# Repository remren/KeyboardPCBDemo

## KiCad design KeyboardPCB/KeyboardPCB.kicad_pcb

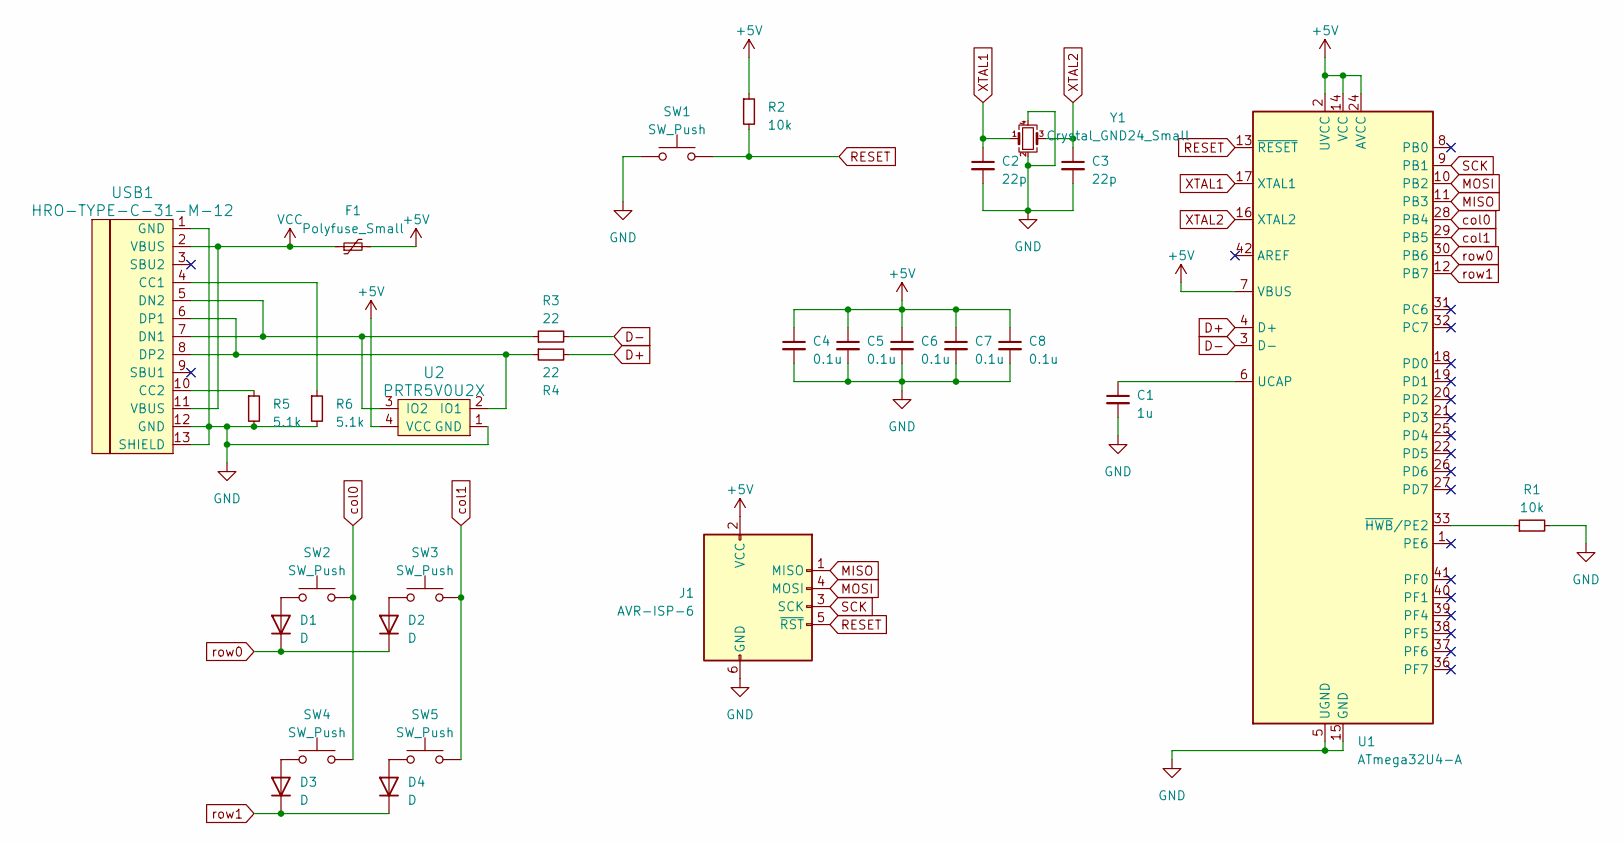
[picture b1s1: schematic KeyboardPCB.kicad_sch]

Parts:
C1: 1u; C_0805_2012Metric_Pad1.18x1.45mm_HandSolder
C2, C3: 22p; C_0805_2012Metric_Pad1.18x1.45mm_HandSolder
C4, C5, C6, C7, C8: 0.1u; C_0805_2012Metric_Pad1.18x1.45mm_HandSolder
D1, D2, D3, D4: D; D_SOD-123
F1: Polyfuse_Small; Fuse_1206_3216Metric_Pad1.42x1.75mm_HandSolder
J1: AVR-ISP-6; Reset_Pretty-Mask
R1, R2: 10k; R_0805_2012Metric_Pad1.20x1.40mm_HandSolder
R3, R4: 22; R_0805_2012Metric_Pad1.20x1.40mm_HandSolder
R5, R6: 5.1k; R_0805_2012Metric_Pad1.20x1.40mm_HandSolder
SW1: SW_Push; SW_SPST_SKQG_WithStem
SW2, SW3, SW4, SW5: SW_Push; MX-1U-NoLED
U1: ATmega32U4-A; TQFP-44_10x10mm_P0.8mm
U2: PRTR5V0U2X; SOT143B
USB1: HRO-TYPE-C-31-M-12; HRO-TYPE-C-31-M-12-HandSoldering
Y1: Crystal_GND24_Small; Crystal_SMD_3225-4Pin_3.2x2.5mm_HandSoldering

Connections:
+5V: C4.1, C5.1, C6.1, C7.1, C8.1, F1.2, J1.2 (VCC), R2.1, U1.2 (UVCC), U1.7 (VBUS), U1.14 (VCC), U1.24 (AVCC), U1.34 (VCC), U1.44 (AVCC), U2.4 (VCC)
D+: R4.2, U1.4 (D+)
D-: R3.2, U1.3 (D-)
GND: C1.2, C2.2, C3.2, C4.2, C5.2, C6.2, C7.2, C8.2, J1.6 (GND), R1.2, R5.2, R6.2, SW1.1, U1.5 (UGND), U1.15 (GND), U1.23 (GND), U1.35 (GND), U1.43 (GND), U2.1 (GND), USB1.1 (GND), USB1.12 (GND), USB1.13 (SHIELD), Y1.2, Y1.4
MISO: J1.1 (MISO), U1.11 (PB3)
MOSI: J1.4 (MOSI), U1.10 (PB2)
unnamed: D1.2 (A), SW2.1
unnamed: D2.2 (A), SW3.1
unnamed: D3.2 (A), SW4.1
unnamed: D4.2 (A), SW5.1
unnamed: C1.1, U1.6 (UCAP)
unnamed: R1.1, U1.33 (~HWB/PE2)
unnamed: R4.1, U2.2 (IO1), USB1.6 (DP1), USB1.8 (DP2)
unnamed: R3.1, U2.3 (IO2), USB1.5 (DN2), USB1.7 (DN1)
unnamed: R6.1, USB1.4 (CC1)
unnamed: R5.1, USB1.10 (CC2)
RESET: J1.5 (~RST), R2.2, SW1.2, U1.13 (~RESET)
SCK: J1.3 (SCK), U1.9 (PB1)
VCC: F1.1, USB1.2 (VBUS), USB1.11 (VBUS)
XTAL1: C2.1, U1.17 (XTAL1), Y1.1
XTAL2: C3.1, U1.16 (XTAL2), Y1.3
col0: SW2.2, SW4.2, U1.28 (PB4)
col1: SW3.2, SW5.2, U1.29 (PB5)
row0: D1.1 (K), D2.1 (K), U1.30 (PB6)
row1: D3.1 (K), D4.1 (K), U1.12 (PB7)

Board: 2 copper layers, 29 parts (0 on the bottom side), 25 nets, no tracks yet.

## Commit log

2023-04-21 KiCad Setup
2023-04-21 stopping point
